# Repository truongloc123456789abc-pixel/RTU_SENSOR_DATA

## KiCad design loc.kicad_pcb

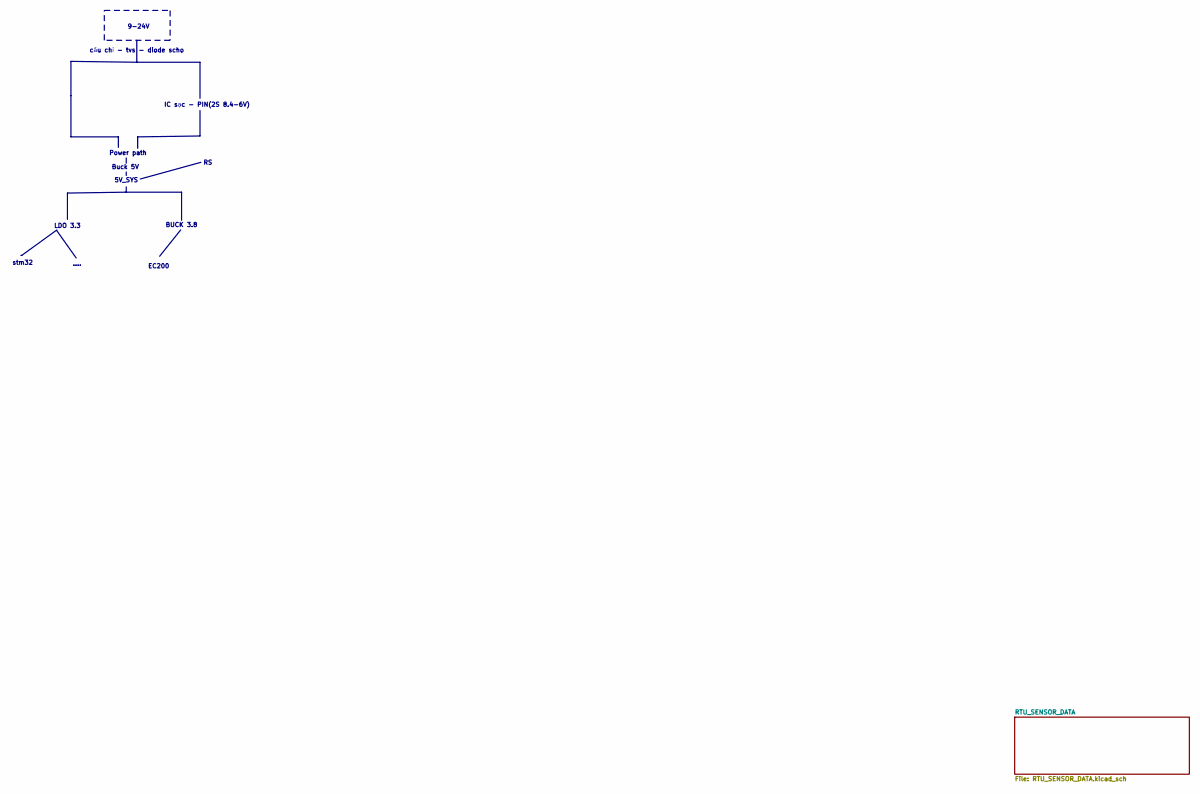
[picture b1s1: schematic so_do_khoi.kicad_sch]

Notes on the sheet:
....
Power path
stm32
IC sạc - PIN(2S 8.4-6V)
9-24V
Buck 5V
LDO 3.3
cầu chỉ - tvs - diode scho
5V_SYS
EC200
BUCK 3.8

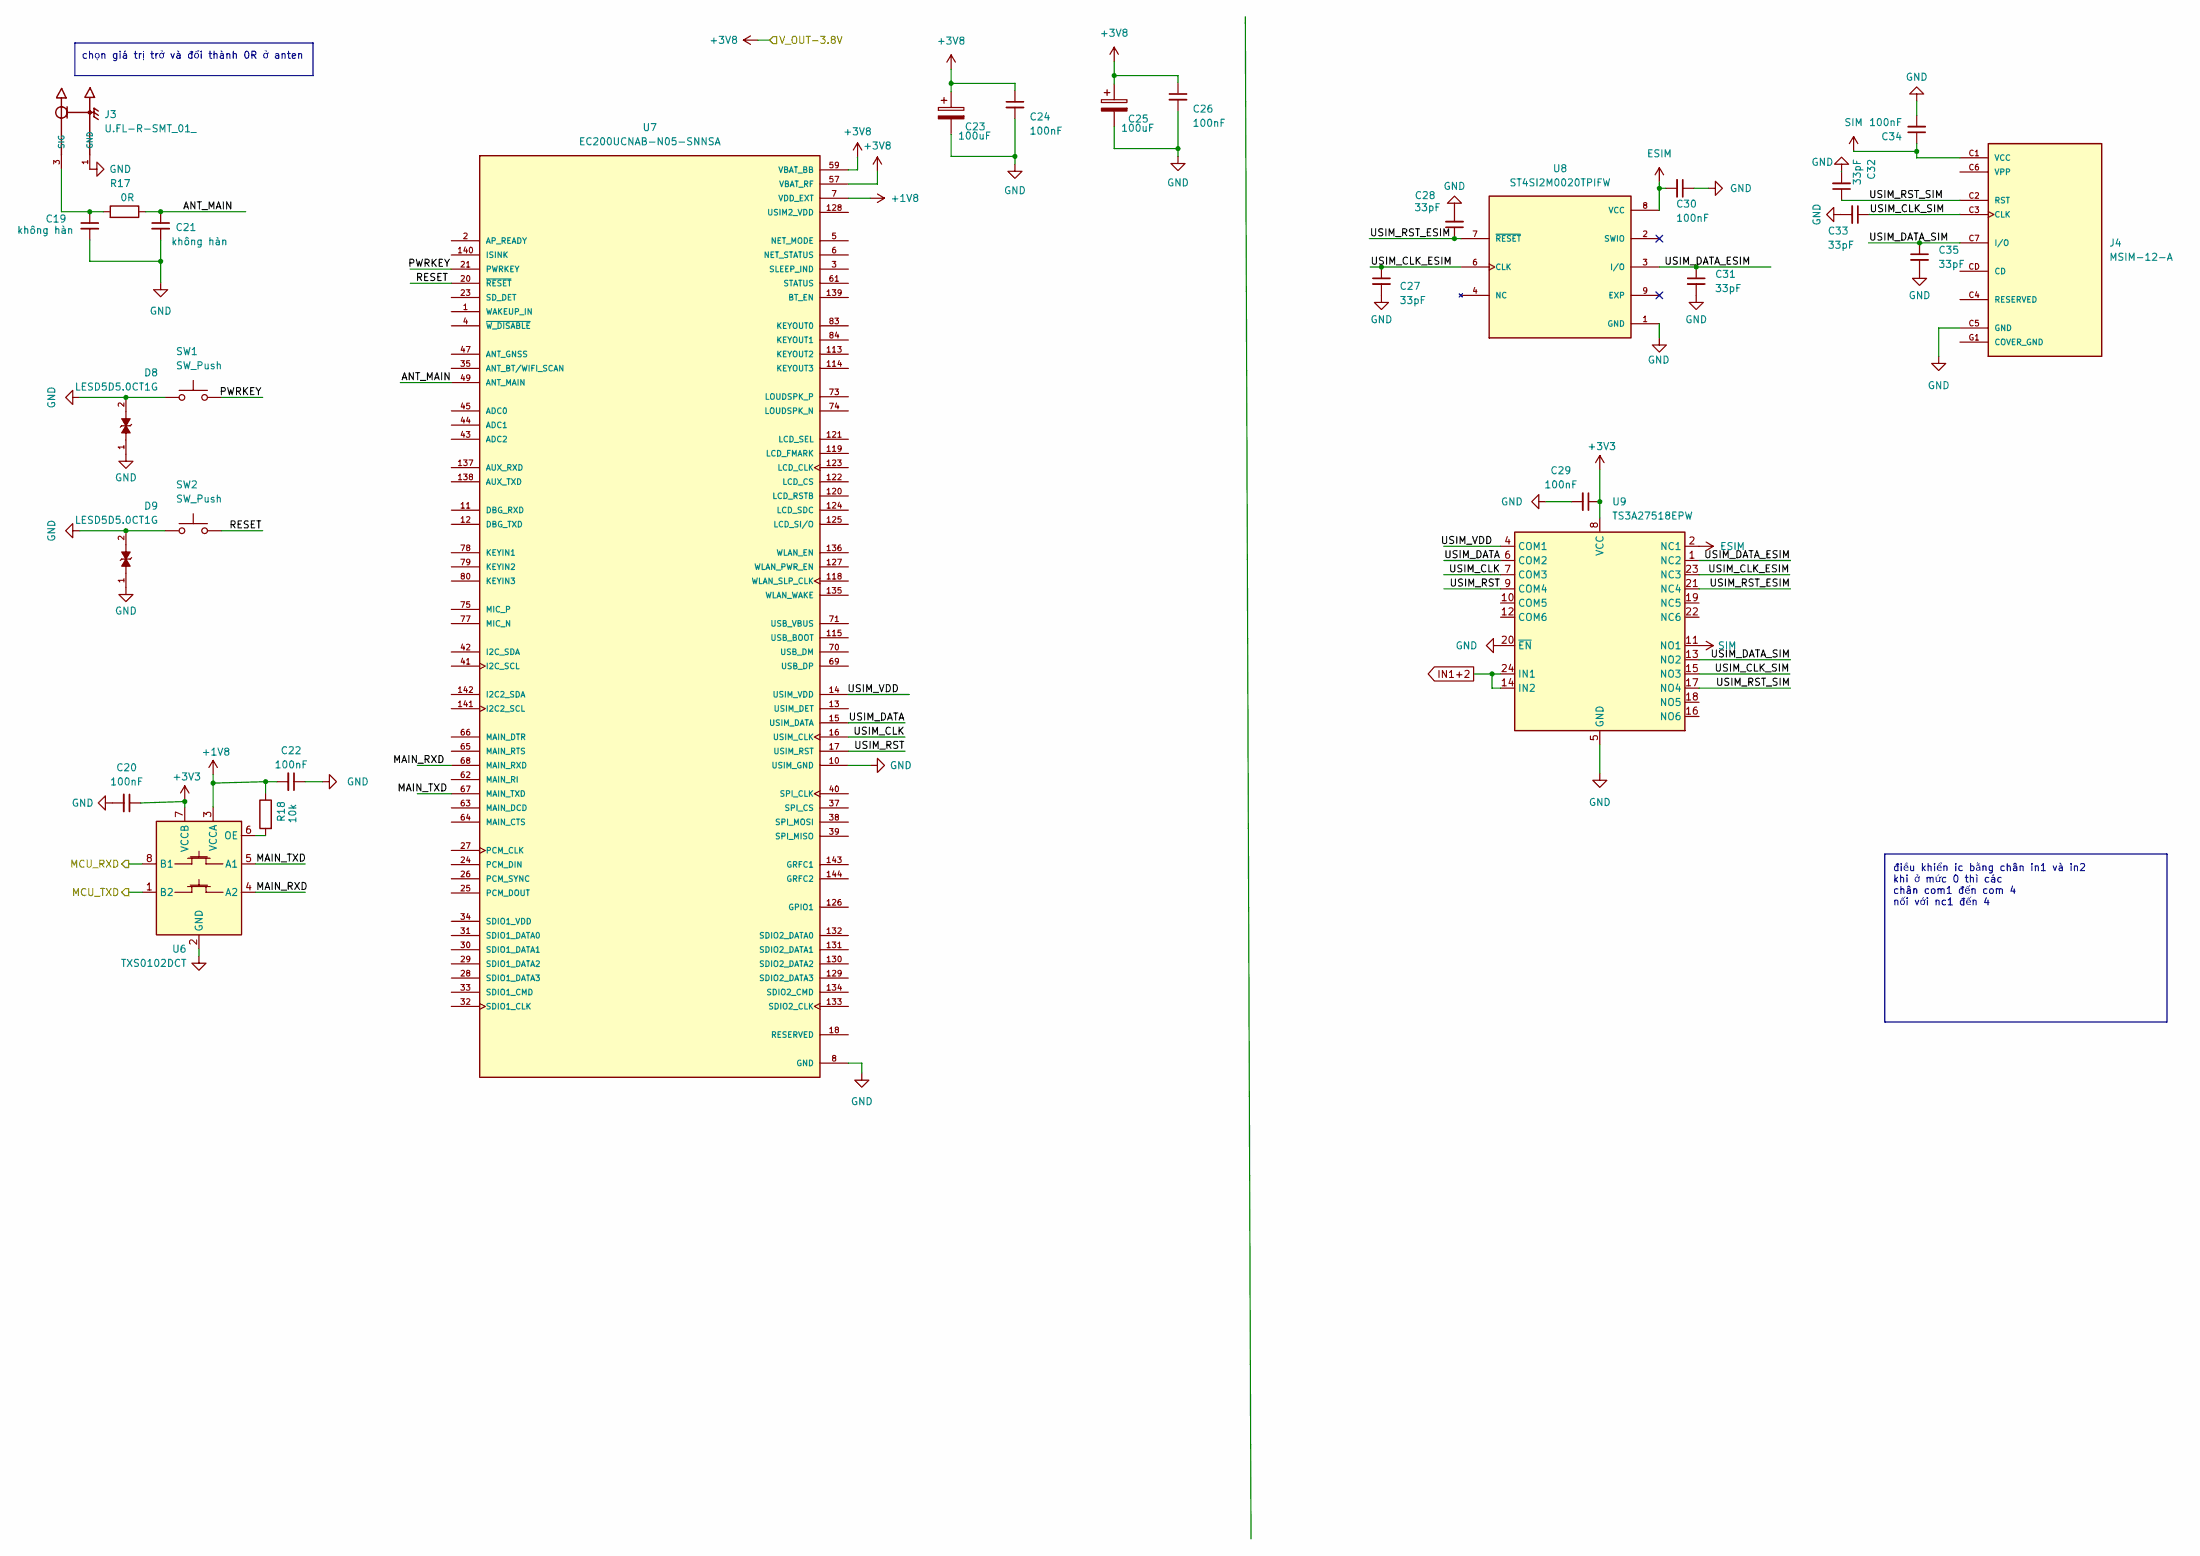
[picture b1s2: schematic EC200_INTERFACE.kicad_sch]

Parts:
C19, C21: không hàn; C_0805_2012Metric
C20, C22, C24, C26, C29, C30, C34: 100nF; C_0805_2012Metric
C23, C25: 100uF; CP_EIA-3528-12_Kemet-T_HandSolder
C27, C28, C31, C32, C33, C35: 33pF; C_0805_2012Metric
D8, D9: LESD5D5.0CT1G; TVS_LESD5D5.0CT1G; PARTREV O
J3: U.FL-R-SMT_01_; HRS_U.FL-R-SMT_01_
J4: MSIM-12-A; CUI_MSIM-12-A; PARTREV 1.0
R17: 0R; R_0805_2012Metric
R18: 10k; R_0805_2012Metric
SW1, SW2: SW_Push; SW_SPST_B3U-1000P
U6: TXS0102DCT; SSOP-8_2.95x2.8mm_P0.65mm
U7: EC200UCNAB-N05-SNNSA; XCVR_EC200UCNAB-N05-SNNSA; PARTREV 1.0
U8: ST4SI2M0020TPIFW; SON127P500X600X100-9N; PARTREV 5
U9: TS3A27518EPW; TSSOP-24_4.4x7.8mm_P0.65mm

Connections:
+1V8: C22.2, R18.1, U6.3 (VCCA), U7.7 (VDD_EXT)
+3V3: C20.1, C29.1, U6.7 (VCCB), U9.8 (VCC); also elsewhere on the board
+3V8: C23.1, C24.1, C25.1, C26.1, U7.57 (VBAT_RF), U7.58 (VBAT_RF), U7.59 (VBAT_BB), U7.60 (VBAT_BB); also elsewhere on the board
/so_do_khoi/RTU_SENSOR_DATA/EC200_INTERFACE/ANT_MAIN: C21.1, R17.1, U7.49 (ANT_MAIN)
/so_do_khoi/RTU_SENSOR_DATA/EC200_INTERFACE/MAIN_RXD: U6.4 (A2), U7.68 (MAIN_RXD)
/so_do_khoi/RTU_SENSOR_DATA/EC200_INTERFACE/MAIN_TXD: U6.5 (A1), U7.67 (MAIN_TXD)
/so_do_khoi/RTU_SENSOR_DATA/EC200_INTERFACE/MCU_RXD: U6.8 (B1); also elsewhere on the board
/so_do_khoi/RTU_SENSOR_DATA/EC200_INTERFACE/MCU_TXD: U6.1 (B2); also elsewhere on the board
/so_do_khoi/RTU_SENSOR_DATA/EC200_INTERFACE/PWRKEY: SW1.1, U7.21 (PWRKEY)
/so_do_khoi/RTU_SENSOR_DATA/EC200_INTERFACE/RESET: SW2.1, U7.20 (~RESET)
/so_do_khoi/RTU_SENSOR_DATA/EC200_INTERFACE/USIM_CLK: U7.16 (USIM_CLK), U9.7 (COM3)
/so_do_khoi/RTU_SENSOR_DATA/EC200_INTERFACE/USIM_CLK_ESIM: C27.1, U8.6 (CLK), U9.23 (NC3)
/so_do_khoi/RTU_SENSOR_DATA/EC200_INTERFACE/USIM_CLK_SIM: C33.1, J4.C3 (CLK), U9.15 (NO3)
/so_do_khoi/RTU_SENSOR_DATA/EC200_INTERFACE/USIM_DATA: U7.15 (USIM_DATA), U9.6 (COM2)
/so_do_khoi/RTU_SENSOR_DATA/EC200_INTERFACE/USIM_DATA_ESIM: C31.1, U8.3 (I/O), U9.1 (NC2)
/so_do_khoi/RTU_SENSOR_DATA/EC200_INTERFACE/USIM_DATA_SIM: C35.1, J4.C7 (I/O), U9.13 (NO2)
/so_do_khoi/RTU_SENSOR_DATA/EC200_INTERFACE/USIM_RST: U7.17 (USIM_RST), U9.9 (COM4)
/so_do_khoi/RTU_SENSOR_DATA/EC200_INTERFACE/USIM_RST_ESIM: C28.1, U8.7 (~RESET), U9.21 (NC4)
/so_do_khoi/RTU_SENSOR_DATA/EC200_INTERFACE/USIM_RST_SIM: C32.1, J4.C2 (RST), U9.17 (NO4)
/so_do_khoi/RTU_SENSOR_DATA/EC200_INTERFACE/USIM_VDD: U7.14 (USIM_VDD), U9.4 (COM1)
COVER_GND: J4.G1 (COVER_GND), J4.G2 (COVER_GND), J4.G3 (COVER_GND), J4.G4 (COVER_GND)
ESIM: C30.2, U8.8 (VCC), U9.2 (NC1)
GND: C19.2, C20.2, C21.2, C22.1, C23.2, C24.2, C25.2, C26.2, C27.2, C28.2, C29.2, C30.1, C31.2, C32.2, C33.2, C34.2, C35.2, D8.1, D8.2, D9.1, D9.2, J3.1 (GND), J3.2 (GND), J4.C5 (GND), SW1.2, SW2.2, U6.2 (GND), U7.8 (GND), U7.9 (GND), U7.10 (USIM_GND), U7.19 (GND), U7.22 (GND), U7.36 (GND), U7.46 (GND), U7.48 (GND), U7.50 (GND), U7.51 (GND), U7.52 (GND), U7.53 (GND), U7.54 (GND), U7.56 (GND), U7.72 (GND), U7.76 (GND), U7.85 (GND), U7.86 (GND), U7.87 (GND), U7.88 (GND), U7.89 (GND), U7.90 (GND), U7.91 (GND), U7.92 (GND), U7.93 (GND), U7.94 (GND), U7.95 (GND), U7.96 (GND), U7.97 (GND), U7.98 (GND), U7.99 (GND), U7.100 (GND), U7.101 (GND), U7.102 (GND), U7.103 (GND), U7.104 (GND), U7.105 (GND), U7.106 (GND), U7.107 (GND), U7.108 (GND), U7.109 (GND), U7.110 (GND), U7.111 (GND), U7.112 (GND), U8.1 (GND), U9.5 (GND), U9.20 (~EN); also elsewhere on the board
IN1+2: U9.14 (IN2), U9.24 (IN1); also elsewhere on the board
unnamed: C19.1, J3.3 (SIG), R17.2
unnamed: J4.C4 (RESERVED), J4.C8 (RESERVED)
unnamed: R18.2, U6.6 (OE)
unnamed: U7.18 (RESERVED), U7.55 (RESERVED), U7.81 (RESERVED), U7.82 (RESERVED), U7.116 (RESERVED), U7.117 (RESERVED)
SIM: C34.1, J4.C1 (VCC), U9.11 (NO1)

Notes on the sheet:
chọn giá trị trở và đổi thành 0R ở anten
điều khiển ic bằng chân in1 và in2 khi ở mức 0 thì các chân com1 đến com 4 nối với nc1 đến 4

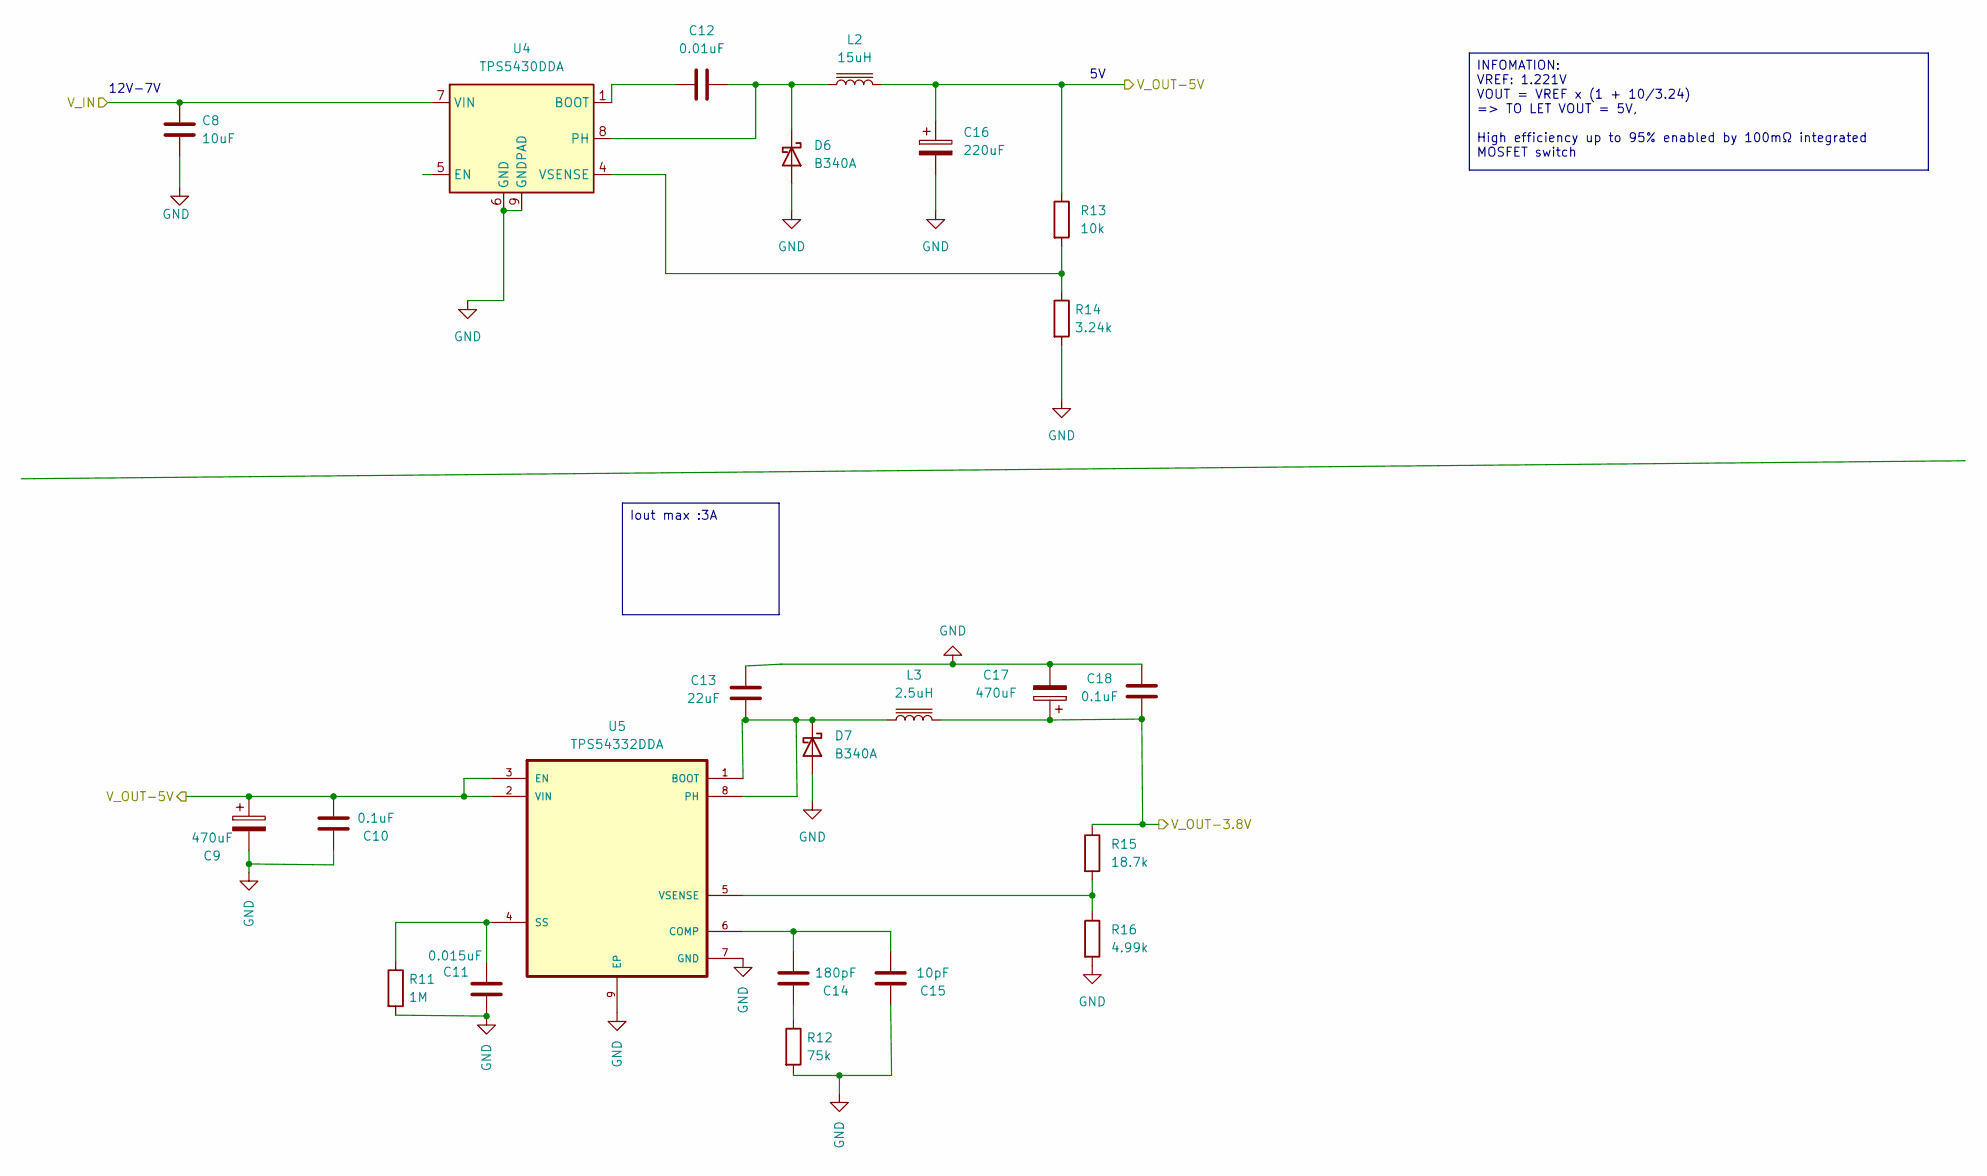
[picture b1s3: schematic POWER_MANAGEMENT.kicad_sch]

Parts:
C8: 10uF; C_0805_2012Metric_Pad1.18x1.45mm_HandSolder
C9, C17: 470uF; CP_EIA-7343-31_Kemet-D
C10, C18: 0.1uF; C_0805_2012Metric_Pad1.18x1.45mm_HandSolder
C11: 0.015uF; C_0805_2012Metric_Pad1.18x1.45mm_HandSolder
C12: 0.01uF; C_0805_2012Metric_Pad1.18x1.45mm_HandSolder
C13: 22uF; C_0805_2012Metric_Pad1.18x1.45mm_HandSolder
C14: 180pF; C_0805_2012Metric_Pad1.18x1.45mm_HandSolder
C15: 10pF; C_0805_2012Metric_Pad1.18x1.45mm_HandSolder
C16: 220uF; CP_EIA-7343-31_Kemet-D
D6, D7: B340A; D_SMC
L2: 15uH; L_Abracon_ASPI-0425
L3: 2.5uH; L_Abracon_ASPI-0425
R11: 1M; R_0805_2012Metric
R12: 75k; R_0805_2012Metric
R13: 10k; R_0805_2012Metric
R14: 3.24k; R_0805_2012Metric
R15: 18.7k; R_0805_2012Metric
R16: 4.99k; R_0805_2012Metric
U4: TPS5430DDA; TI_SO-PowerPAD-8_ThermalVias
U5: TPS54332DDA; VREG_LM5017MR_NOPB

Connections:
+3V8: C17.1, C18.2, L3.2, R15.1; also elsewhere on the board
/so_do_khoi/RTU_SENSOR_DATA/BQ24610_POWER_CHARGE/VSYSTEM: C8.1, U4.7 (VIN); also elsewhere on the board
/so_do_khoi/RTU_SENSOR_DATA/MCU/V_OUT-5V: C9.1, C10.2, C16.1, L2.2, R13.1, U5.2 (VIN), U5.3 (EN); also elsewhere on the board
GND: C8.2, C9.2, C10.1, C11.1, C13.1, C15.1, C16.2, C17.2, C18.1, D6.2 (A), D7.2 (A), R11.2, R12.2, R14.2, R16.2, U4.6 (GND), U4.9 (GNDPAD), U5.7 (GND), U5.9 (EP); also elsewhere on the board
unnamed: C14.1, R12.1
unnamed: C12.2, D6.1 (K), L2.1, U4.8 (PH)
unnamed: C13.2, D7.1 (K), L3.1, U5.1 (BOOT), U5.8 (PH)
unnamed: C12.1, U4.1 (BOOT)
unnamed: R13.2, R14.1, U4.4 (VSENSE)
unnamed: C14.2, C15.2, U5.6 (COMP)
unnamed: C11.2, R11.1, U5.4 (SS)
unnamed: R15.2, R16.1, U5.5 (VSENSE)

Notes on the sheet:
12V-7V
Iout max :3A
INFOMATION: VREF: 1.221V VOUT = VREF x (1 + 10/3.24) => TO LET VOUT = 5V, High efficiency up to 95% enabled by 100mΩ integrated MOSFET switch

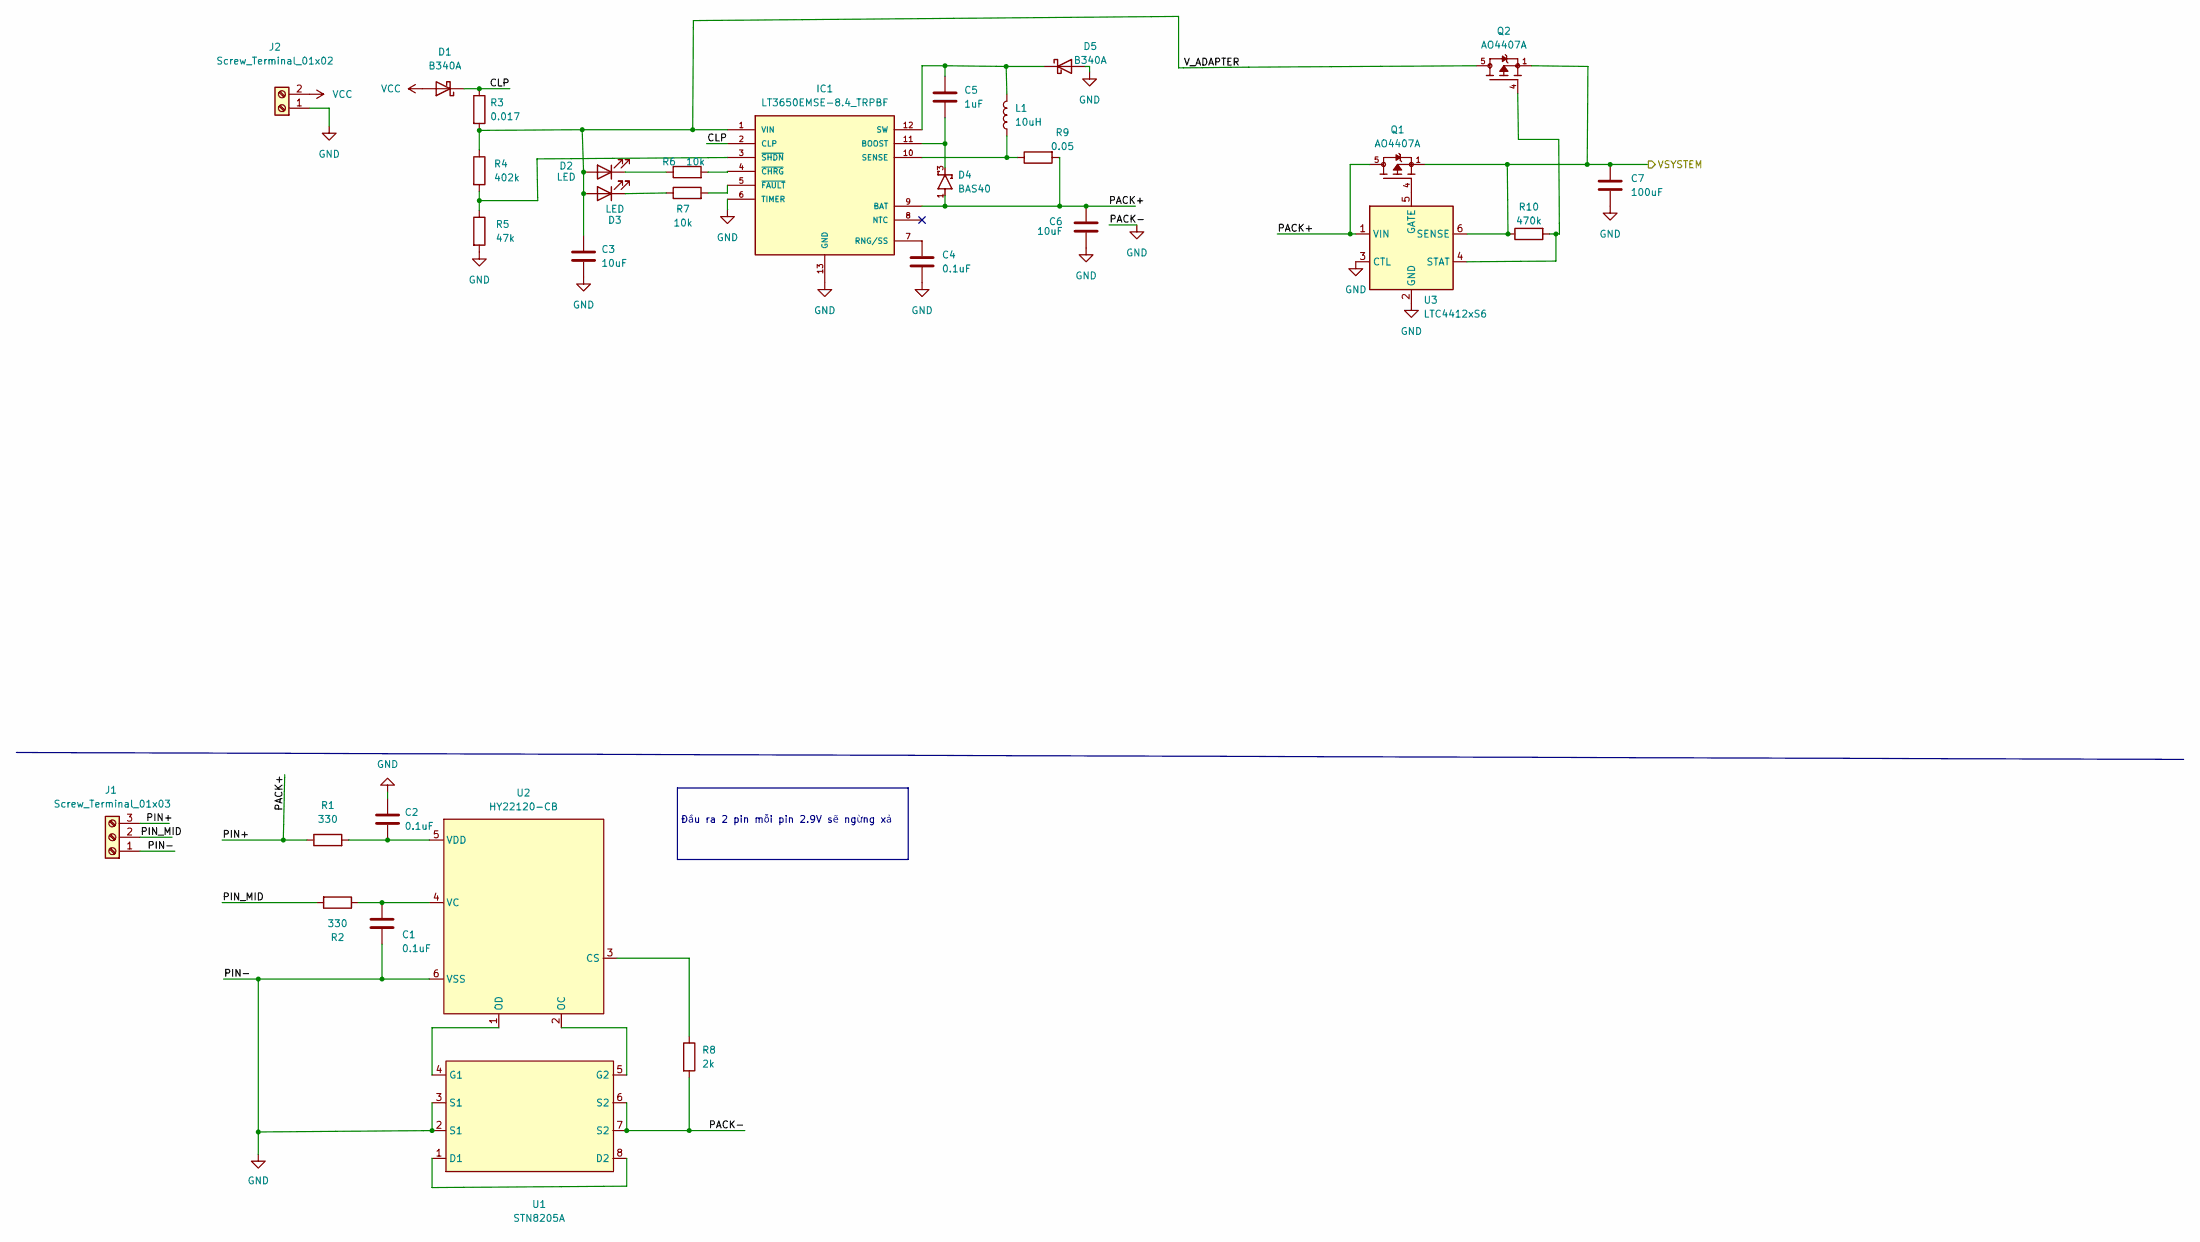
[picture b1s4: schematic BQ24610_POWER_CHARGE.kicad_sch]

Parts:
C1, C2, C4: 0.1uF; C_0805_2012Metric_Pad1.18x1.45mm_HandSolder
C3, C6: 10uF; C_0805_2012Metric_Pad1.18x1.45mm_HandSolder
C5: 1uF; C_0805_2012Metric_Pad1.18x1.45mm_HandSolder
C7: 100uF; C_0805_2012Metric_Pad1.18x1.45mm_HandSolder
D1, D5: B340A; D_SMC
D2, D3: LED; LED_0805_2012Metric_Pad1.15x1.40mm_HandSolder
D4: BAS40; SOT23
IC1: LT3650EMSE-8.4_TRPBF; SOP65P490X110-13N; MOUSER_PART_NUMBER 584-3650EMSE-4.2PBF
J1: Screw_Terminal_01x03; TerminalBlock_Phoenix_PT-1,5-3-3.5-H_1x03_P3.50mm_Horizontal
J2: Screw_Terminal_01x02; TerminalBlock_Phoenix_MKDS-3-2-5.08_1x02_P5.08mm_Horizontal
L1: 10uH; L_Abracon_ASPI-0425
Q1, Q2: AO4407A; SOIC127P600X175-8N; PARTREV I
R1, R2: 330; R_0805_2012Metric
R3: 0.017; R_0805_2012Metric
R4: 402k; R_0805_2012Metric
R5: 47k; R_0805_2012Metric
R6, R7: 10k; R_0805_2012Metric
R8: 2k; R_0805_2012Metric
R9: 0.05; R_0805_2012Metric
R10: 470k; R_0805_2012Metric
U1: STN8205A; TSSOP-8_4.4x3mm_P0.65mm
U2: HY22120-CB; SOT-23-6
U3: LTC4412xS6; TSOT-23-6

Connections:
/so_do_khoi/RTU_SENSOR_DATA/BQ24610_POWER_CHARGE/CLP: D1.1 (K), IC1.2 (CLP), R3.1
/so_do_khoi/RTU_SENSOR_DATA/BQ24610_POWER_CHARGE/PACK+: C6.1, D4.1, IC1.9 (BAT), J1.3, Q1.5, Q1.6, Q1.7, Q1.8, R1.1, R9.2, U3.1 (VIN)
/so_do_khoi/RTU_SENSOR_DATA/BQ24610_POWER_CHARGE/PIN_MID: J1.2, R2.2
/so_do_khoi/RTU_SENSOR_DATA/BQ24610_POWER_CHARGE/VSYSTEM: C7.1, Q1.1, Q1.2, Q1.3, Q2.1, Q2.2, Q2.3, R10.1, U3.6 (SENSE); also elsewhere on the board
/so_do_khoi/RTU_SENSOR_DATA/BQ24610_POWER_CHARGE/V_ADAPTER: C3.1, D2.2 (A), D3.2 (A), IC1.1 (VIN), Q2.5, Q2.6, Q2.7, Q2.8, R3.2, R4.1
GND: C1.1, C2.1, C3.2, C4.2, C6.2, C7.2, D5.2 (A), IC1.6 (TIMER), IC1.13 (GND), J1.1, J2.1, R5.2, R8.2, U1.2 (S1), U1.3 (S1), U1.6 (S2), U1.7 (S2), U2.6 (VSS), U3.2 (GND), U3.3 (CTL); also elsewhere on the board
unnamed: D2.1 (K), R6.1
unnamed: D3.1 (K), R7.1
unnamed: C5.1, D5.1 (K), IC1.12 (SW), L1.2
unnamed: C5.2, D4.3, IC1.11 (BOOST)
unnamed: C4.1, IC1.7 (RNG/SS)
unnamed: IC1.10 (SENSE), L1.1, R9.1
unnamed: IC1.4 (~CHRG), R6.2
unnamed: IC1.5 (~FAULT), R7.2
unnamed: IC1.3 (~SHDN), R4.2, R5.1
unnamed: U1.1 (D1), U1.8 (D2)
unnamed: U1.4 (G1), U2.1 (OD)
unnamed: U1.5 (G2), U2.2 (OC)
unnamed: R8.1, U2.3 (CS)
unnamed: C1.2, R2.1, U2.4 (VC)
unnamed: C2.2, R1.2, U2.5 (VDD)
unnamed: Q1.4, U3.5 (GATE)
unnamed: Q2.4, R10.2, U3.4 (STAT)
VCC: D1.2 (A), J2.2

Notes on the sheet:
Đầu ra 2 pin mỗi pin 2.9V sẽ ngừng xả

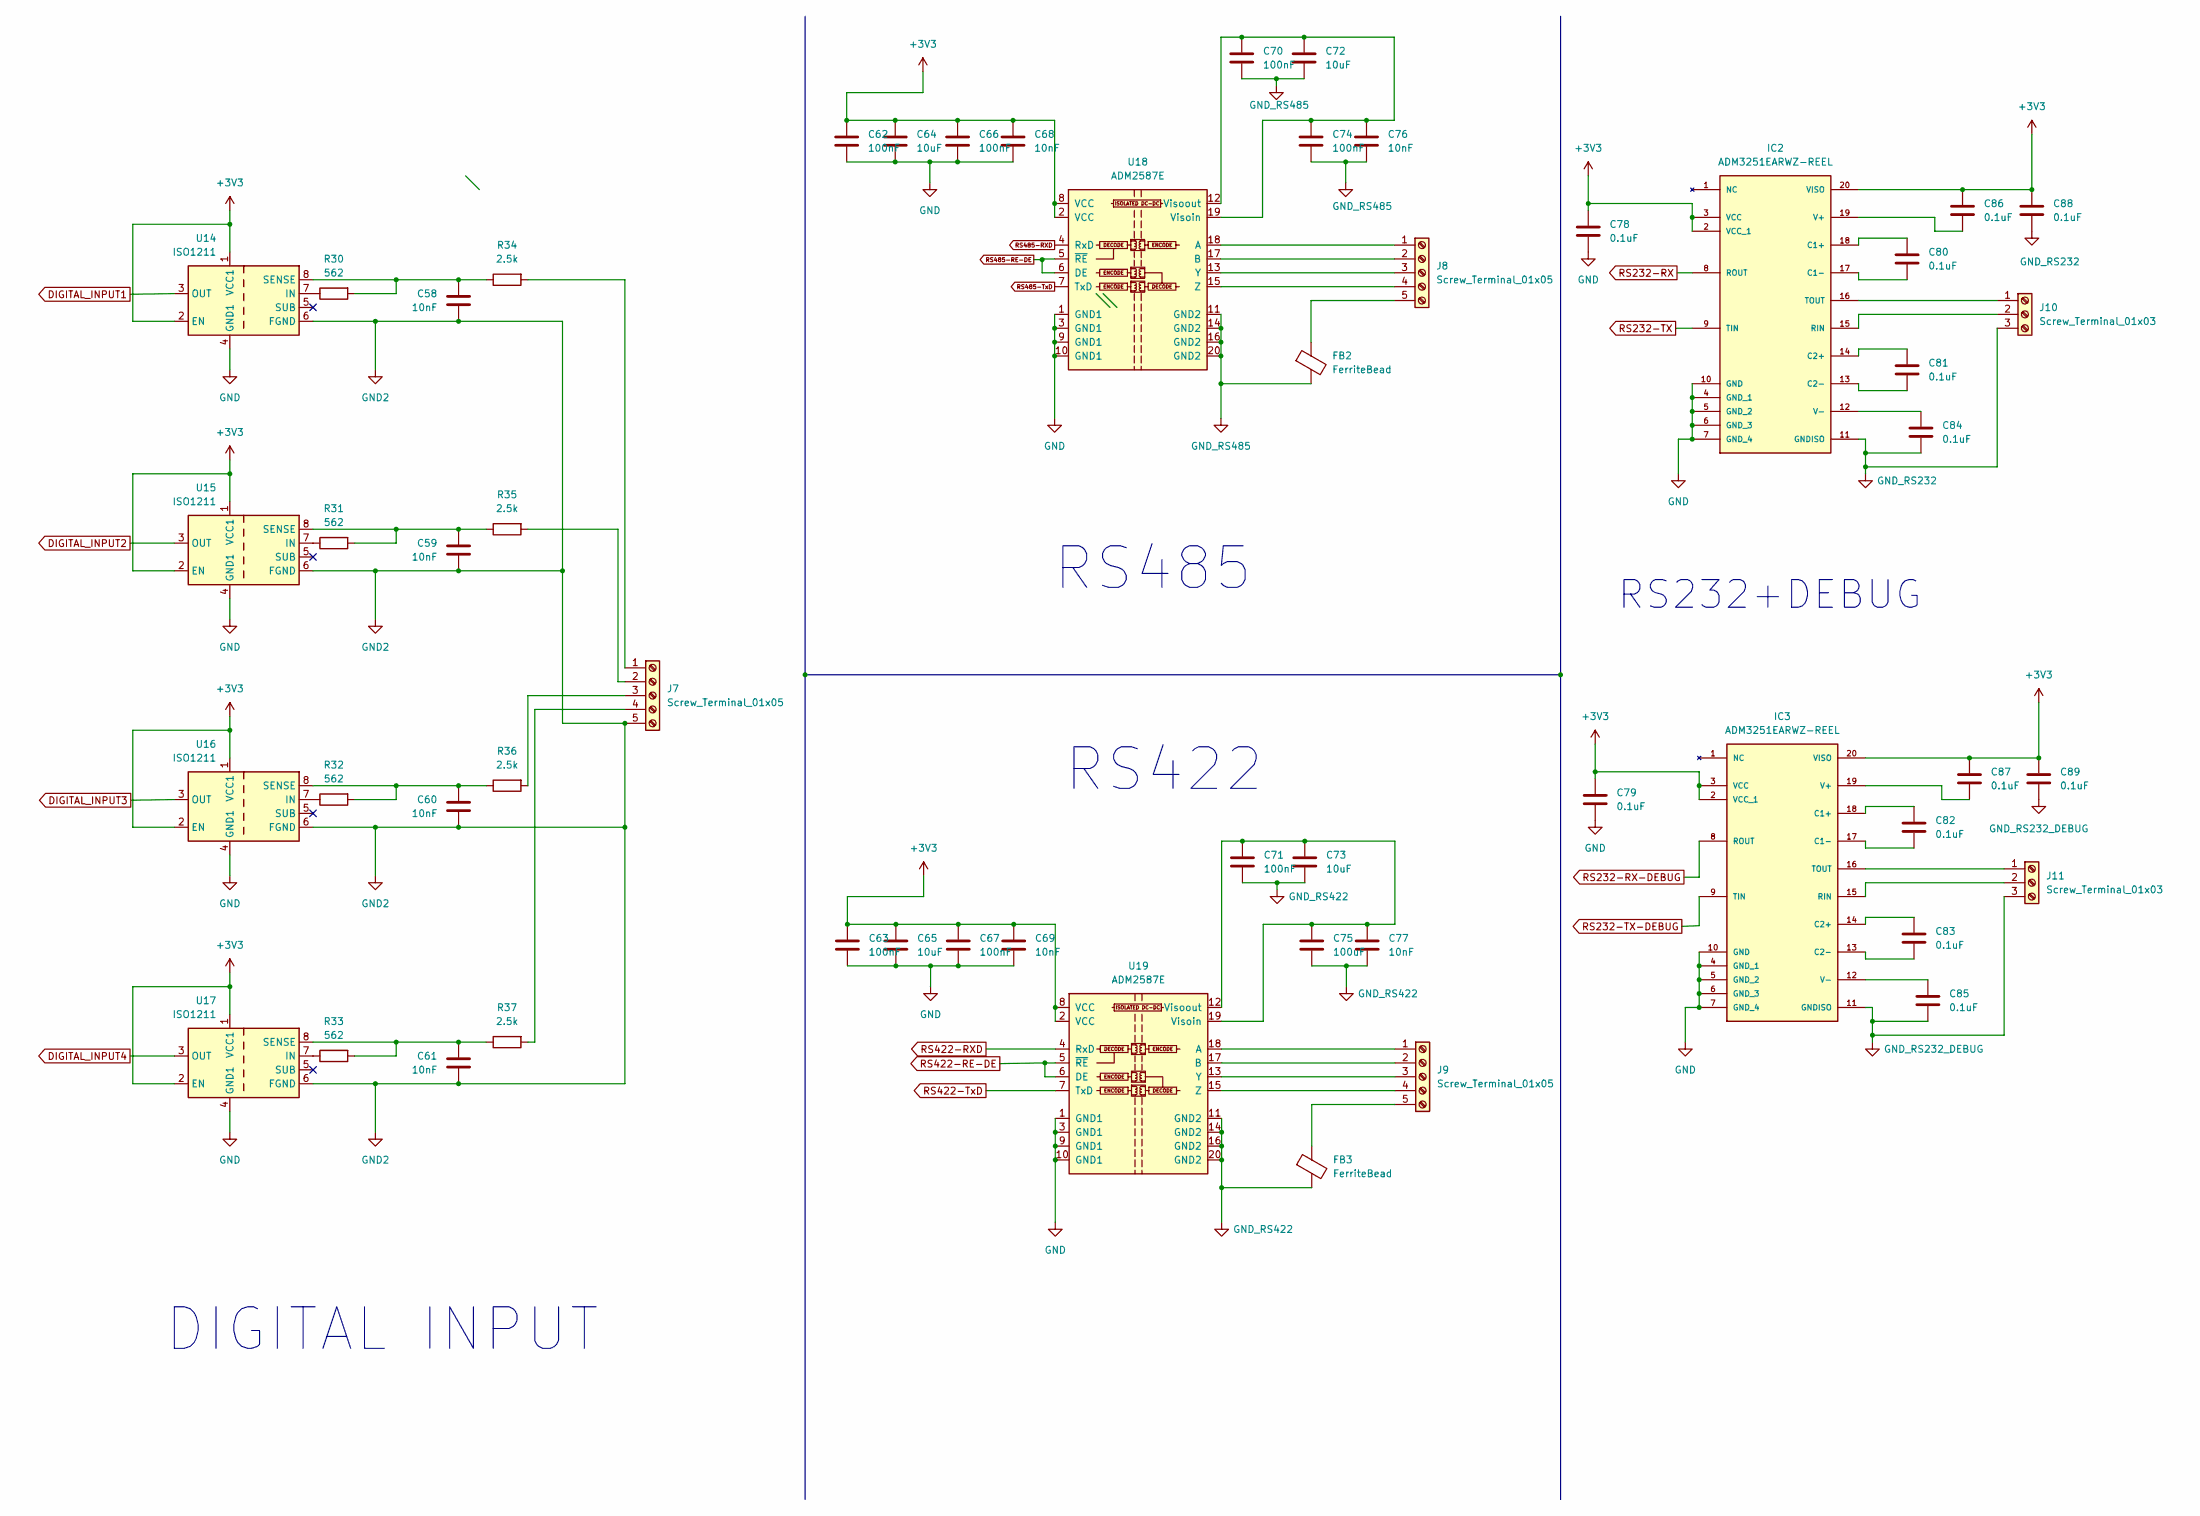
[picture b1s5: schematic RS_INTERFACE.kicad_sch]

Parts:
C58, C59, C60, C61, C68, C69, C76, C77: 10nF; C_0805_2012Metric
C62, C63, C66, C67, C70, C71, C74: 100nF; C_0805_2012Metric
C64, C65, C72, C73: 10uF; C_0805_2012Metric
C75: 100uF; C_0805_2012Metric
C78, C79, C80, C81, C82, C83, C84, C85, C86, C87, C88, C89: 0.1uF; C_0805_2012Metric
FB2, FB3: FerriteBead; L_0805_2012Metric
IC2, IC3: ADM3251EARWZ-REEL; SOIC127P1032X265-20N; MOUSER_PART_NUMBER 584-ADM3251EARWZ-R
J7, J8, J9: Screw_Terminal_01x05; TerminalBlock_Phoenix_PT-1,5-5-3.5-H_1x05_P3.50mm_Horizontal
J10, J11: Screw_Terminal_01x03; TerminalBlock_Phoenix_PT-1,5-3-3.5-H_1x03_P3.50mm_Horizontal
R30, R31, R32, R33: 562; R_0805_2012Metric
R34, R35, R36, R37: 2.5k; R_0805_2012Metric
U14, U15, U16, U17: ISO1211; SOIC-8_3.9x4.9mm_P1.27mm
U18, U19: ADM2587E; SOIC-20W_7.5x12.8mm_P1.27mm

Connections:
+3V3: C62.1, C63.1, C64.1, C65.1, C66.1, C67.1, C68.1, C69.1, C78.1, C79.1, C86.1, C87.1, C88.1, C89.1, IC2.2 (VCC_1), IC2.3 (VCC), IC2.20 (VISO), IC3.2 (VCC_1), IC3.3 (VCC), IC3.20 (VISO), U14.1 (VCC1), U14.2 (EN), U15.1 (VCC1), U15.2 (EN), U16.1 (VCC1), U16.2 (EN), U17.1 (VCC1), U17.2 (EN), U18.2 (VCC), U18.8 (VCC), U19.2 (VCC), U19.8 (VCC); also elsewhere on the board
DIGITAL_INPUT1: U14.3 (OUT); also elsewhere on the board
DIGITAL_INPUT2: U15.3 (OUT); also elsewhere on the board
DIGITAL_INPUT3: U16.3 (OUT); also elsewhere on the board
DIGITAL_INPUT4: U17.3 (OUT); also elsewhere on the board
GND: C62.2, C63.2, C64.2, C65.2, C66.2, C67.2, C68.2, C69.2, C78.2, C79.2, IC2.4 (GND_1), IC2.5 (GND_2), IC2.6 (GND_3), IC2.7 (GND_4), IC2.10 (GND), IC3.4 (GND_1), IC3.5 (GND_2), IC3.6 (GND_3), IC3.7 (GND_4), IC3.10 (GND), U14.4 (GND1), U15.4 (GND1), U16.4 (GND1), U17.4 (GND1), U18.1 (GND1), U18.3 (GND1), U18.9 (GND1), U18.10 (GND1), U19.1 (GND1), U19.3 (GND1), U19.9 (GND1), U19.10 (GND1); also elsewhere on the board
GND2: C58.2, C59.2, C60.2, C61.2, J7.5, U14.6 (FGND), U15.6 (FGND), U16.6 (FGND), U17.6 (FGND)
GND_RS232: C84.2, C88.2, IC2.11 (GNDISO), J10.3
GND_RS232_DEBUG: C85.2, C89.2, IC3.11 (GNDISO), J11.3
GND_RS422: C71.2, C73.2, C75.2, C77.2, FB3.2, U19.11 (GND2), U19.14 (GND2), U19.16 (GND2), U19.20 (GND2)
GND_RS485: C70.2, C72.2, C74.2, C76.2, FB2.2, U18.11 (GND2), U18.14 (GND2), U18.16 (GND2), U18.20 (GND2)
unnamed: C80.1, IC2.18 (C1+)
unnamed: C80.2, IC2.17 (C1-)
unnamed: C81.1, IC2.14 (C2+)
unnamed: C81.2, IC2.13 (C2-)
unnamed: IC2.15 (RIN), J10.2
unnamed: IC2.16 (TOUT), J10.1
unnamed: C86.2, IC2.19 (V+)
unnamed: C84.1, IC2.12 (V-)
unnamed: C82.1, IC3.18 (C1+)
unnamed: C82.2, IC3.17 (C1-)
unnamed: C83.1, IC3.14 (C2+)
unnamed: C83.2, IC3.13 (C2-)
unnamed: IC3.15 (RIN), J11.2
unnamed: IC3.16 (TOUT), J11.1
unnamed: C87.2, IC3.19 (V+)
unnamed: C85.1, IC3.12 (V-)
unnamed: J7.1, R34.2
unnamed: J7.2, R35.2
unnamed: J7.3, R36.2
unnamed: J7.4, R37.2
unnamed: J8.1, U18.18 (A)
unnamed: J8.2, U18.17 (B)
unnamed: J8.3, U18.13 (Y)
unnamed: J8.4, U18.15 (Z)
unnamed: FB2.1, J8.5
unnamed: J9.1, U19.18 (A)
unnamed: J9.2, U19.17 (B)
unnamed: J9.3, U19.13 (Y)
unnamed: J9.4, U19.15 (Z)
unnamed: FB3.1, J9.5
unnamed: R30.1, U14.7 (IN)
unnamed: C58.1, R30.2, R34.1, U14.8 (SENSE)
unnamed: R31.1, U15.7 (IN)
unnamed: C59.1, R31.2, R35.1, U15.8 (SENSE)
unnamed: R32.1, U16.7 (IN)
unnamed: C60.1, R32.2, R36.1, U16.8 (SENSE)
unnamed: R33.1, U17.7 (IN)
unnamed: C61.1, R33.2, R37.1, U17.8 (SENSE)
unnamed: C70.1, C72.1, C74.1, C76.1, U18.12 (Visoout), U18.19 (Visoin)
unnamed: C71.1, C73.1, C75.1, C77.1, U19.12 (Visoout), U19.19 (Visoin)
RS232-RX: IC2.8 (ROUT); also elsewhere on the board
RS232-RX-DEBUG: IC3.8 (ROUT); also elsewhere on the board
RS232-TX: IC2.9 (TIN); also elsewhere on the board
RS232-TX-DEBUG: IC3.9 (TIN); also elsewhere on the board
RS422-RE-DE: U19.5 (~RE), U19.6 (DE); also elsewhere on the board
RS422-RXD: U19.4 (RxD); also elsewhere on the board
RS422-TxD: U19.7 (TxD); also elsewhere on the board
RS485-RE-DE: U18.5 (~RE), U18.6 (DE); also elsewhere on the board
RS485-RXD: U18.4 (RxD); also elsewhere on the board
RS485-TxD: U18.7 (TxD); also elsewhere on the board

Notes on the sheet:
RS422
DIGITAL INPUT
RS485
RS232+DEBUG
